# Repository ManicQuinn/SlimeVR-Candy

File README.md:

# Candy-Case (Not Maintained Anymore due to moving on to my [Smol-Slimes Design](https://github.com/ManicQuinn/SlimeVR-Gremlin))
A Non-PCB case for SlimeVR trackers, over engineered and optimized for being compact. They're only 61.8mm(L)x60.5(W)x16.2mm(H) in size WITH strap loops, and only weigh about 50 grams with all the components inside and wired up(Including the battery I chose, your millage may vary).

I've looked at every problem available to me at a technical level, from cable routing causing issues with the Wifi antenna, to a size problem when it comes to Non-PCB cases, the goal of this project was to be as optimized as I could. There were some issues I could not fix due to the design, and decided to compromise.

The issues are as follows:
1. The D1 Mini's USB port is inaccesible when you close up the case, this is due to me wanting the antenna to be close to the walls and away from all the cables. Not a huge issue in my opinion as you'll only need this to flash the firmware, calibration can be done wirelessly, a bit hard tho.
2. Soldering it is a lot harder than other cases due to the layout I chose as it is incredibly compact, and the IMU being under the D1 Mini makes it hard as well.
3. You will need to cut up a battery holder or some kind of battery contacts for your 14500 battery as these are designed with DIY battery contacts in mind, these can't be too thick either, I chose to cut one up with flush cutters and super glue them in place.
4. Double sided tape might be required for some parts, I used it for the IMU because cable tension kept pushing it into a non-flat position and also used tape on the lid to keep the switch from sliding into the case as the lid has a slight issue, you can also super glue the switch in, I opted not to.

Parts: 
1. Wemos D1 Mini V4.0
2. BMI160
3. TP4056 (Type C version)
4. SS12D10 Switch
5. Some kind of battery contacts, I used a cut up BH-311-1A AA Battery Holder
6. 14500 Lithium-Ion Battery 800-1000mAh, I used a Vapcell H10 as they're rated well
7. M2 screws, 8mm in length, Countersunk Flat Heads
8. M2 Heat threaded insert (OD)3.5mm (H)6mm

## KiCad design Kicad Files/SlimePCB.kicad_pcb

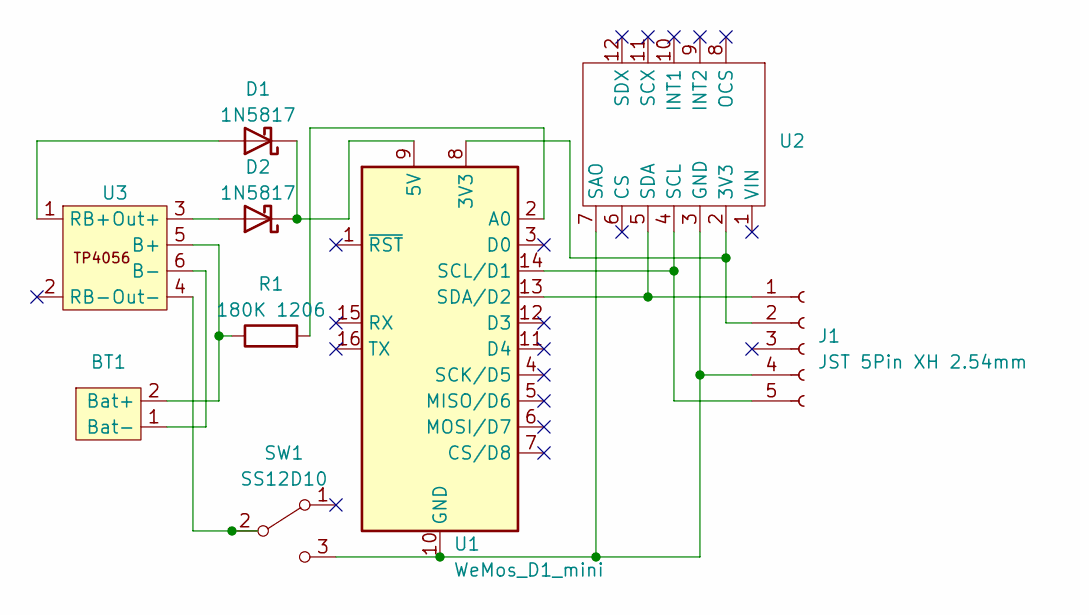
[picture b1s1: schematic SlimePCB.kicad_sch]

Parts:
BT1: Battery
D1, D2: 1N5817; DO-214AC
J1: JST 5Pin XH 2.54mm; JST_XH_S5B-XH-A_1x05_P2.50mm_Horizontal
R1: 180K 1206; R_1206_3216Metric_Pad1.30x1.75mm_HandSolder
SW1: SS12D10
U1: WeMos_D1_mini; WEMOS_D1_mini_light
U2: BMI160 module
U3: TP4056-18650

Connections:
unnamed: BT1.2 (Bat+), R1.1, U3.5 (B+)
unnamed: BT1.1 (Bat-), U3.6 (B-)
unnamed: D1.C (K), D2.C (K), U1.9 (5V)
unnamed: J1.1, U1.13 (SDA/D2), U2.5 (SDA)
unnamed: J1.2, U1.8 (3V3), U2.2 (3V3)
unnamed: J1.4, SW1.3 (C), U1.10 (GND), U2.3 (GND), U2.7 (SAO)
unnamed: J1.5, U1.14 (SCL/D1), U2.4 (SCL)
unnamed: SW1.2 (B), U3.4 (Out-)
unnamed: R1.2, U1.2 (A0)
unnamed: D2.A, U3.3 (Out+)
unnamed: D1.A, U3.1 (RB+)

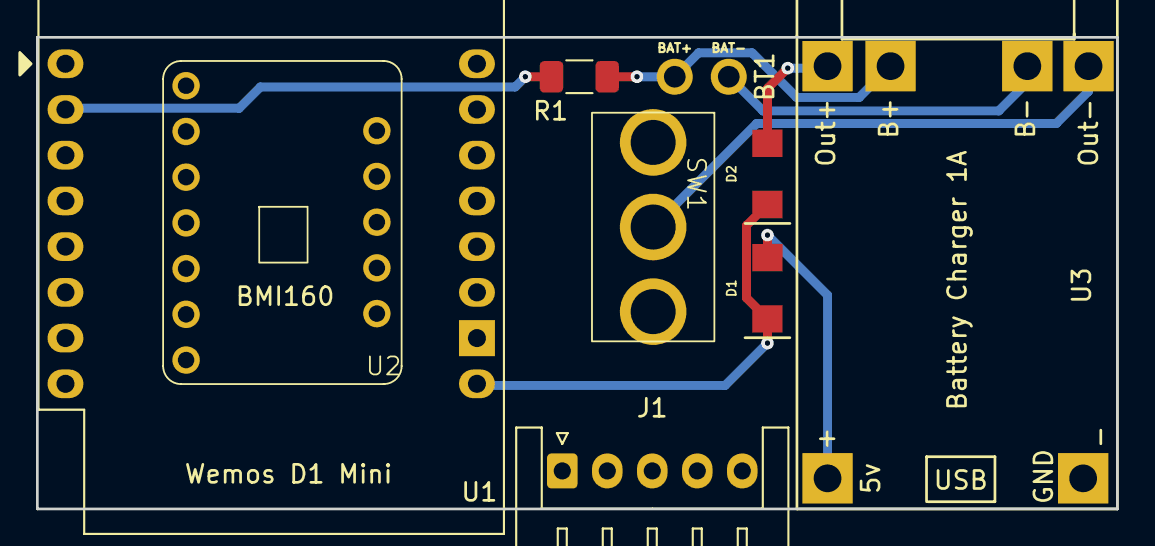
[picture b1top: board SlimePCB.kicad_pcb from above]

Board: 2 copper layers, 60.0 x 26.2 mm, 9 parts (0 on the bottom side), 11 nets.

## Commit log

2023-09-23 Changed layout
    Things to do
    Learn how to add ground pours, signal return paths, stitching vias, ground vias
2023-09-23 Forgot Schematic
2023-10-09 Rename ReadMe.txt to ReadMe.txt
2023-10-09 Added 3D case files along with renaming Kicad Files to WIP
2023-10-09 Changed main Readme.txt
2023-10-18 Updated to V2, changed quite a bit after first prototype.
2023-10-21 Updated to V3.0, Thickened a lot of stuff, including strap loops, changed some stuff on the inside, including walls to hold in the D1 Mini.
2023-10-22 Updated to V4.0, moved to a permanent cable Aux design instead of removable JST, added some fillets in the case in the battery area, moved the screw stem for the lid so that you can use it to constra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
2023-10-22 Updated to V4.1, very minor update, shrinked the lid by 0.1mm.
2023-10-22 Updated to V4.2, changed fillet on screw hole to chamfer, added fillet to charging hole
2023-10-22 Added photos to README.md
2023-10-22 Updated to V4.3, very minor change, just adjusted the end stop for the screw so it doesn't go so deep.
2023-10-22 Added parts to README.md
2023-10-23 Updated to V5.0. Important update from V4.0. Added fillets everywhere I could to make 3D printing easier, Fixed Switch Dimensions as they were very wrong before, adjusted D1 Mini height in the case t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
2023-10-28 Massive update from V5.0 as I finally had a test print of version 5, had to make a ton of changes to fix a ton of issues. Full change log below:
    Strap Loop was changed to be smaller and fit 38mm/1.5 inch straps, Lid was adjusted to 3mm thick, made tons of changes to tolerences of parts, moved screw hole, moved D1 LED hole as they were wrong b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
2023-10-29 Updated to Ver.7.0: Redesigned the lid to still be 3mm but made a 1mm space for the battery as it wouldn't fit otherwise after rereviewing tolerences. Made a slight change in one of the fillets on th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
2023-11-10 Updated to V8.1. Bunch of tolerance changes from V7.0 and had a successful print, all parts fit but still needs more work, next version might be the final version, released as the true V1.0. Honestly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
2023-11-12 Updated to V8.3. Change log: D1 Mini V4.0 Tolerence reduced to fit better, TP4056 and D1 LED holes changed, D1 Mini LED still needs to be adjust further in next version. Aux Hole was moved higher up 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
2023-11-15 Final Update for Main tracker:
    - A lid "opening" gap on the edge of case to easily open the lid.
    - A "hole and peg" on the battery side so that it locks in this area, as I found that a single screw would not be enough because the battery would push against the lid when loose, worrying during fas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
    - Strap Loop increased gap by 1mm.
    - D1 Mini LED Hole adjusted as it is off by just a lil bit.
    - Adjusted the distance the screw hole is from the edge by 0.1mm to hopefully help with printing.
    - Battery gap on lid adjusted to 0.4mm instead of the initial 1mm.
2023-11-26 Updated Readme and added new photos
2023-11-26 Fixed photos
2024-06-25 Added V10 f3d file
2024-06-25 Changed the clamp measurements for chest strap.
2024-07-05 Updated V10
